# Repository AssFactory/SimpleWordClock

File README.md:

<div align="center">

# Simple Word Clock

**A Swabian word clock, built with Zephyr RTOS.**

[Features](#features) · [Hardware](#hardware) · [Getting started](#getting-started) · [Documentation](#documentation)

</div>

## Project photos

<!-- Replace these placeholders with photos of the finished clock when available. -->

## Overview

Simple Word Clock is an open-source LED clock that displays the time in Swabian phrasing. Its firmware is built on Zephyr RTOS and runs on the Adafruit ItsyBitsy RP2040.

## Features

- Swabian word-clock display with animated transitions
- Automatic brightness adjustment using an ambient light sensor
- Adjustable brightness and display color
- Battery-backed real-time clock with configurable time zone and daylight saving
- USB serial shell for configuration and diagnostics

## Hardware

The current build uses an Adafruit ItsyBitsy RP2040, a WS2812B LED strip, a DS3231 real-time clock, and a BH1750 light sensor.

## Getting started

Set up the [Zephyr development environment](https://docs.zephyrproject.org/latest/develop/getting_started/index.html), then create a workspace using this repository as the West manifest:

```sh
mkdir word-clock-workspace
cd word-clock-workspace
git clone https://github.com/AssFactory/SimpleWordClock.git
west init -l SimpleWordClock
west update
west build -s SimpleWordClock -b adafruit_itsybitsy_rp2040
```

For firmware releases, see the [GitHub Releases](../../releases).

To build and publish a release automatically, push a version tag such as
`v1.0.0`. GitHub Actions copies the tag version into `VERSION`, builds the UF2
firmware, appends the tagged commit's short Git hash to the firmware version,
and attaches it to the release. The installed version can be read with
`app version` in the USB serial shell:

```sh
git tag v1.0.0
git push origin v1.0.0
```

## Tests

The firmware logic tests use Zephyr's ztest framework and run on the
64-bit `native_sim` simulator. From the West workspace root, run:

```sh
west twister -T SimpleWordClock/tests/wordclock -p native_sim/native/64
```

GitHub Actions runs these tests on pushes and pull requests.

## Documentation

- [User manual (PDF)](docs/SimpleWordClock-User-Manual-A4-Booklet-DE.pdf)
- [User manual (HTML)](docs/SimpleWordClock-User-Manual-DE.html)

## License

Released under the [MIT License](LICENSE).

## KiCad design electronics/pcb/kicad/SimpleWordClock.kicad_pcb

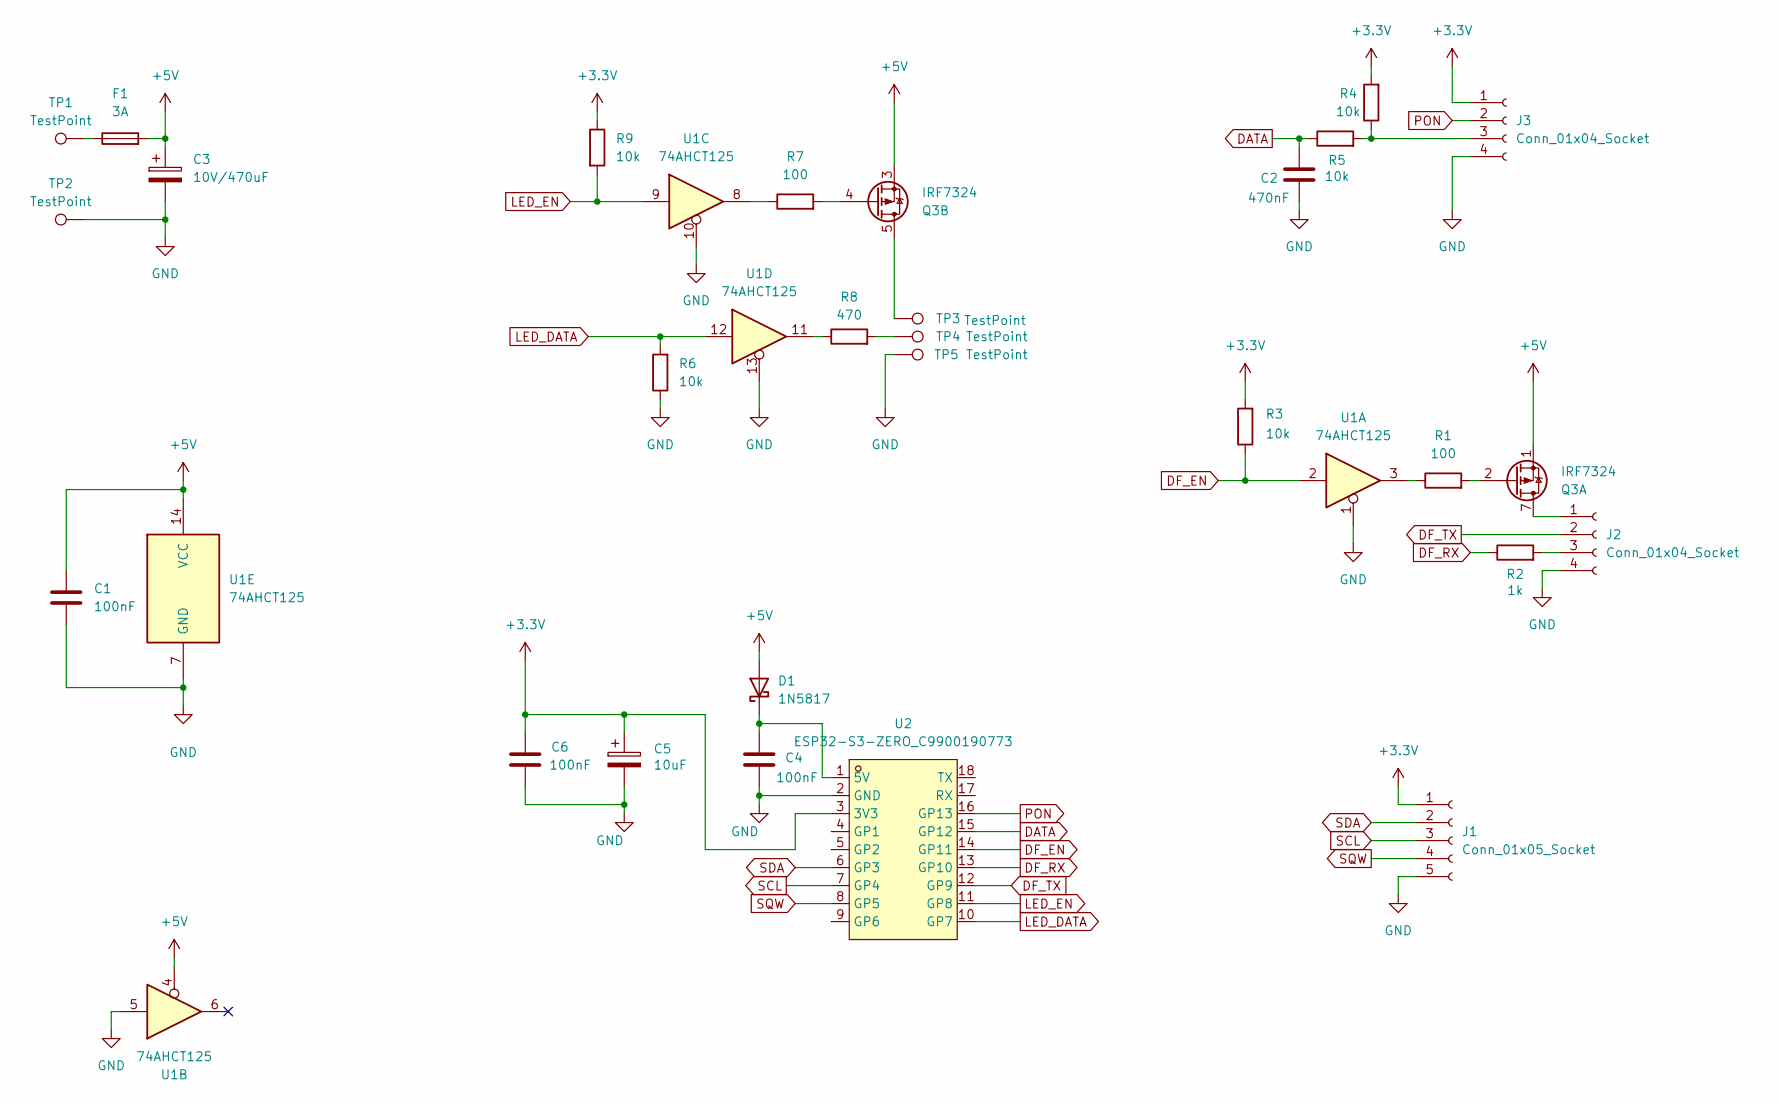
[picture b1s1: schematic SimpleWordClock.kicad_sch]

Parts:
C1, C4, C6: 100nF; C_1210_3225Metric_Pad1.33x2.70mm_HandSolder
C2: 470nF; C_1206_3216Metric_Pad1.33x1.80mm_HandSolder
C3: 10V/470uF; CP_Elec_10x10.5
C5: 10uF; CP_Elec_10x10
D1: 1N5817; D_DO-41_SOD81_P10.16mm_Horizontal
F1: 3A; Fuseholder_Clip-5x20mm_Schurter_CQM_Inline_P20.60x5.00mm_D1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
J1: Conn_01x05_Socket; JST_EH_B5B-EH-A_1x05_P2.50mm_Vertical
J2, J3: Conn_01x04_Socket; JST_EH_B4B-EH-A_1x04_P2.50mm_Vertical
Q3: IRF7324; SOIC-8_3.9x4.9mm_P1.27mm
R1, R7: 100; R_1210_3225Metric_Pad1.30x2.65mm_HandSolder
R2: 1k; R_1210_3225Metric_Pad1.30x2.65mm_HandSolder
R3, R4, R5, R6, R9: 10k; R_1210_3225Metric_Pad1.30x2.65mm_HandSolder
R8: 470; R_1210_3225Metric_Pad1.30x2.65mm_HandSolder
TP1, TP2, TP3, TP5: TestPoint; TestPoint_Pad_4.0x4.0mm
TP4: TestPoint; TestPoint_Pad_3.0x3.0mm
U1: 74AHCT125; DIP-14_W7.62mm_LongPads
U2: ESP32-S3-ZERO_C9900190773; COMM-SMD_18P-L24.5-W17.8-P2.54_ESP32-S3-ZERO; MPN ESP32-S3-Zero; LCSC Part C9900190773

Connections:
+3.3V: C5.1, C6.1, J1.1, J3.1, R3.2, R4.2, R9.1, U2.3 (3V3)
+5V: C1.1, C3.1, D1.2 (A), F1.2, Q3.1 (S1), Q3.3 (S2), U1.4, U1.14 (VCC)
DATA: C2.1, R5.1, U2.15 (GP12)
DF_EN: R3.1, U1.2, U2.14 (GP11)
DF_RX: R2.1, U2.13 (GP10)
DF_TX: J2.2, U2.12 (GP9)
GND: C1.2, C2.2, C3.2, C4.2, C5.2, C6.2, J1.5, J2.4, J3.4, R6.1, TP2.1 (1_1), TP5.1 (1_1), U1.1, U1.5, U1.7 (GND), U1.10, U1.13, U2.2 (GND)
LED_DATA: R6.2, U1.12, U2.10 (GP7)
LED_EN: R9.2, U1.9, U2.11 (GP8)
unnamed: C4.1, D1.1 (K), U2.1 (5V)
unnamed: F1.1, TP1.1 (1_1)
unnamed: J2.1, Q3.7 (D1), Q3.8 (D1)
unnamed: J2.3, R2.2
unnamed: J3.3, R4.1, R5.2
unnamed: Q3.2 (G1), R1.2
unnamed: Q3.5 (D2), Q3.6 (D2), TP3.1 (1_1)
unnamed: Q3.4 (G2), R7.2
unnamed: R1.1, U1.3
unnamed: R7.1, U1.8
unnamed: R8.1, U1.11
unnamed: R8.2, TP4.1 (1_1)
PON: J3.2, U2.16 (GP13)
SCL: J1.3, U2.7 (GP4)
SDA: J1.2, U2.6 (GP3)
SQW: J1.4, U2.8 (GP5)

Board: 2 copper layers, 28 parts (0 on the bottom side), 25 nets, no tracks yet.
